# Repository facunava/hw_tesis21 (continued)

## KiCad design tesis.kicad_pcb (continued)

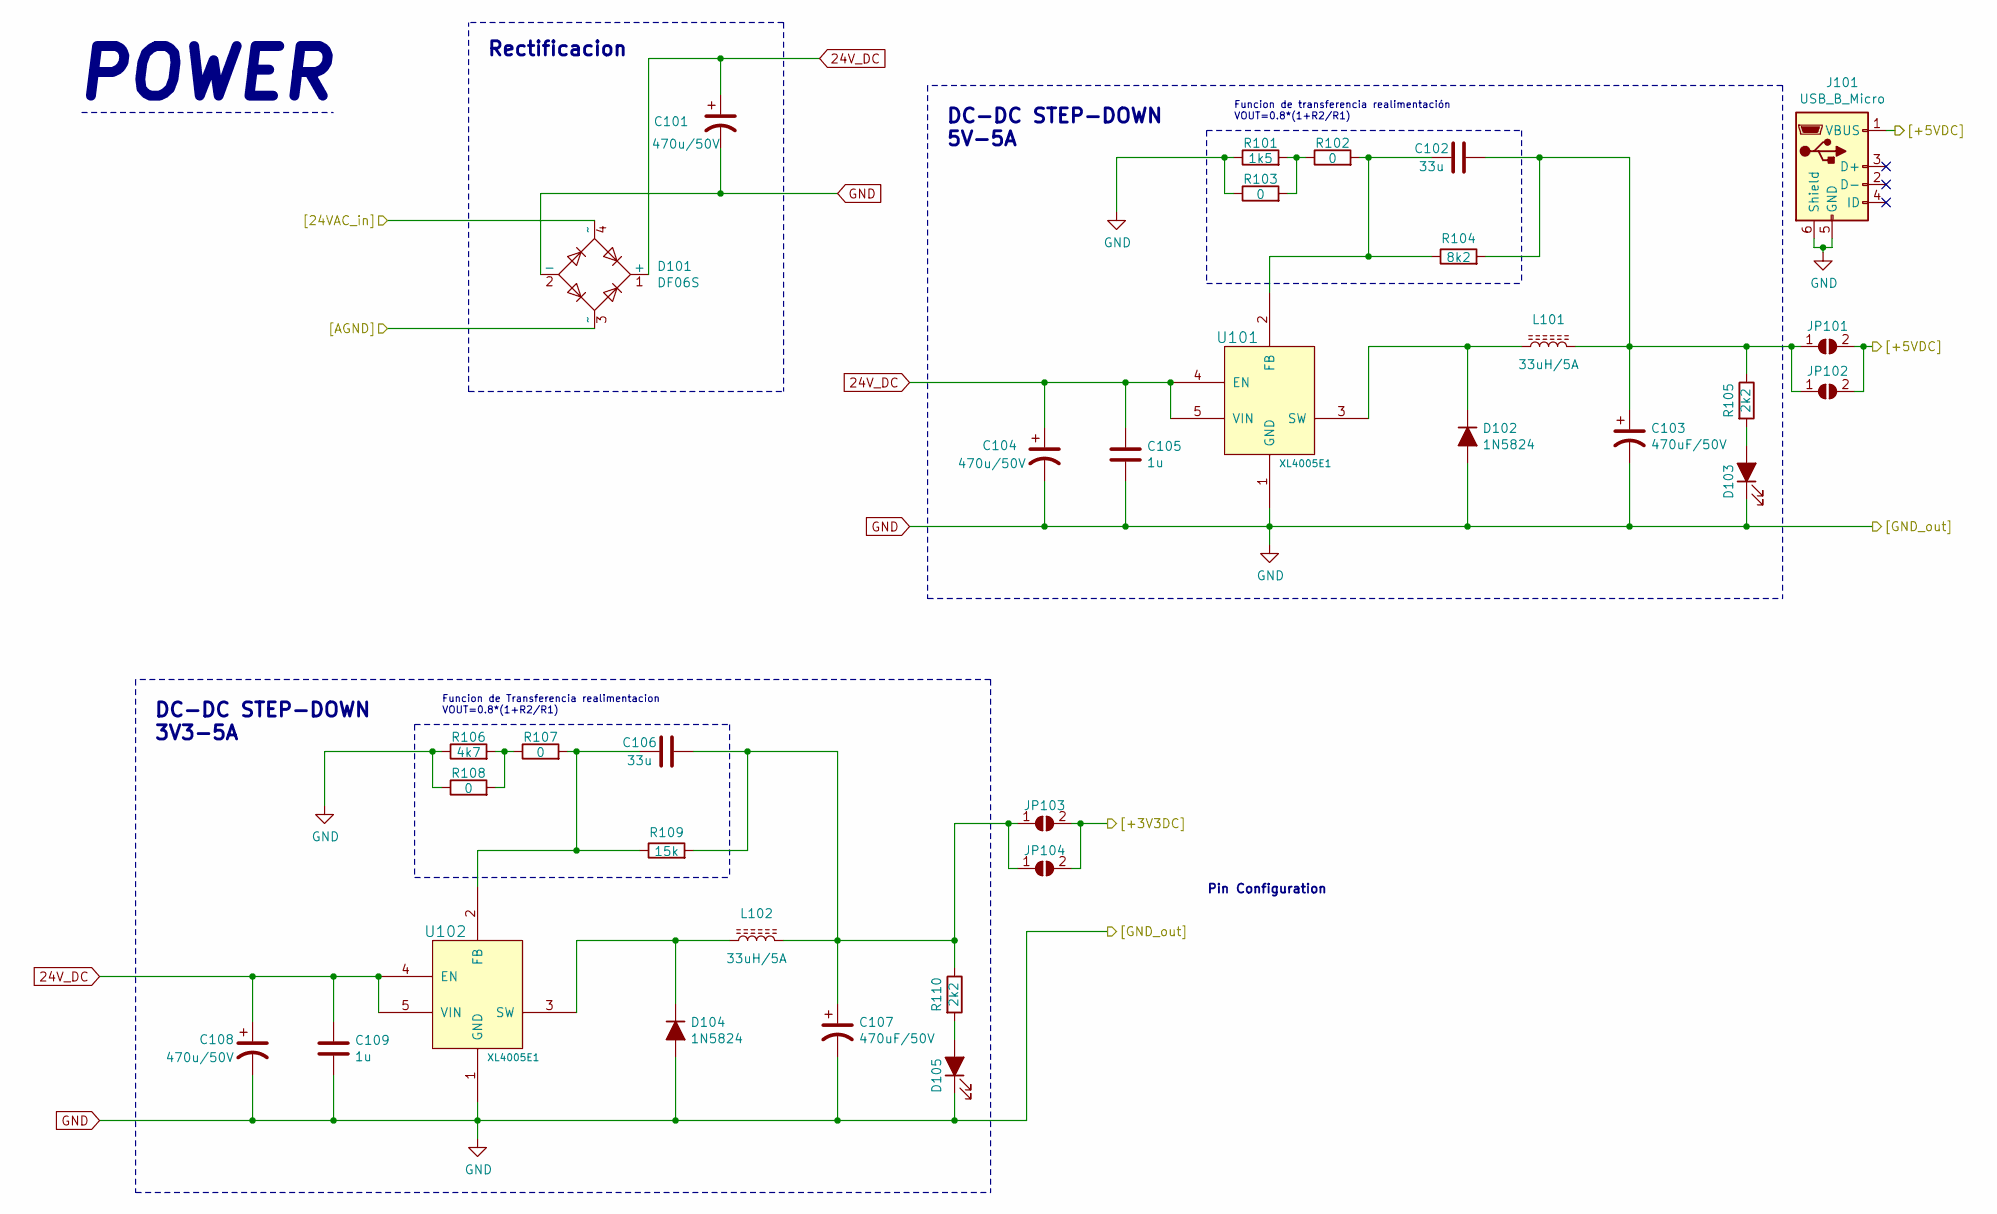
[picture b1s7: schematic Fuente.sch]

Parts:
C101: 470u/50V; CP_Elec_10x10
C102, C106: 33u; C_0805_2012Metric_Pad1.18x1.45mm_HandSolder
C103, C107: 470uF/50V; CP_Elec_8x10.5
C104, C108: 470u/50V; CP_Elec_8x10.5
C105, C109: 1u; C_0805_2012Metric_Pad1.18x1.45mm_HandSolder
D101: DF06S; Diode_Bridge_Vishay_DFSFlat
D102, D104: 1N5824; D_SMB_Handsoldering; PARTREV 2
D103, D105: green; LED_0805_2012Metric_Castellated
J101: USB_B_Micro; USB_Micro-B_Molex_47346-0001
JP101, JP102, JP103, JP104: jumper; SolderJumper-2_P1.3mm_Open_RoundedPad1.0x1.5mm
L101, L102: 33uH/5A; Coil_ferrite
R101: 1k5; R_0805_2012Metric_Pad1.20x1.40mm_HandSolder
R102, R103, R107, R108: 0; R_0805_2012Metric_Pad1.20x1.40mm_HandSolder
R104: 8k2; R_0805_2012Metric_Pad1.20x1.40mm_HandSolder
R105, R110: 2k2; R_0805_2012Metric_Pad1.20x1.40mm_HandSolder
R106: 4k7; R_0805_2012Metric_Pad1.20x1.40mm_HandSolder
R109: 15k; R_0805_2012Metric_Pad1.20x1.40mm_HandSolder
U101, U102: XL4005E1; TO-263-5_TabPin3

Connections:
24V_DC: C101.1, C104.1, C105.1, C108.1, C109.1, D101.1 (+), U101.4 (EN), U101.5 (VIN), U102.4 (EN), U102.5 (VIN)
+3V3: JP103.2 (B), JP104.2 (B); also elsewhere on the board
+5V: J101.1 (VBUS), JP101.2 (B), JP102.2 (B); also elsewhere on the board
/[24VAC_main]: D101.4 (~~); also elsewhere on the board
/[AGND_main]: D101.3 (~~); also elsewhere on the board
GND: C101.2, C103.2, C104.2, C105.2, C107.2, C108.2, C109.2, D101.2 (-), D102.2 (A), D103.1 (K), D104.2 (A), D105.1 (K), J101.5 (GND), J101.6 (Shield), R101.1, R103.1, R106.1, R108.1, U101.1 (GND), U102.1 (GND); also elsewhere on the board
unnamed: C102.1, C103.1, JP101.1 (A), JP102.1 (A), L101.2, R104.2, R105.1
unnamed: C102.2, R102.2, R104.1, U101.2 (FB)
unnamed: C106.1, C107.1, JP103.1 (A), JP104.1 (A), L102.2, R109.2, R110.1
unnamed: C106.2, R107.2, R109.1, U102.2 (FB)
unnamed: D102.1 (K), L101.1, U101.3 (SW)
unnamed: D103.2 (A), R105.2
unnamed: D104.1 (K), L102.1, U102.3 (SW)
unnamed: D105.2 (A), R110.2
unnamed: R101.2, R102.1, R103.2
unnamed: R106.2, R107.1, R108.2

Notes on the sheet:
POWER
DC-DC STEP-DOWN 3V3-5A
Funcion de Transferencia realimentacion VOUT=0.8*(1+R2/R1)
Rectificacion
Funcion de transferencia realimentación VOUT=0.8*(1+R2/R1)
DC-DC STEP-DOWN 5V-5A
Pin Configuration

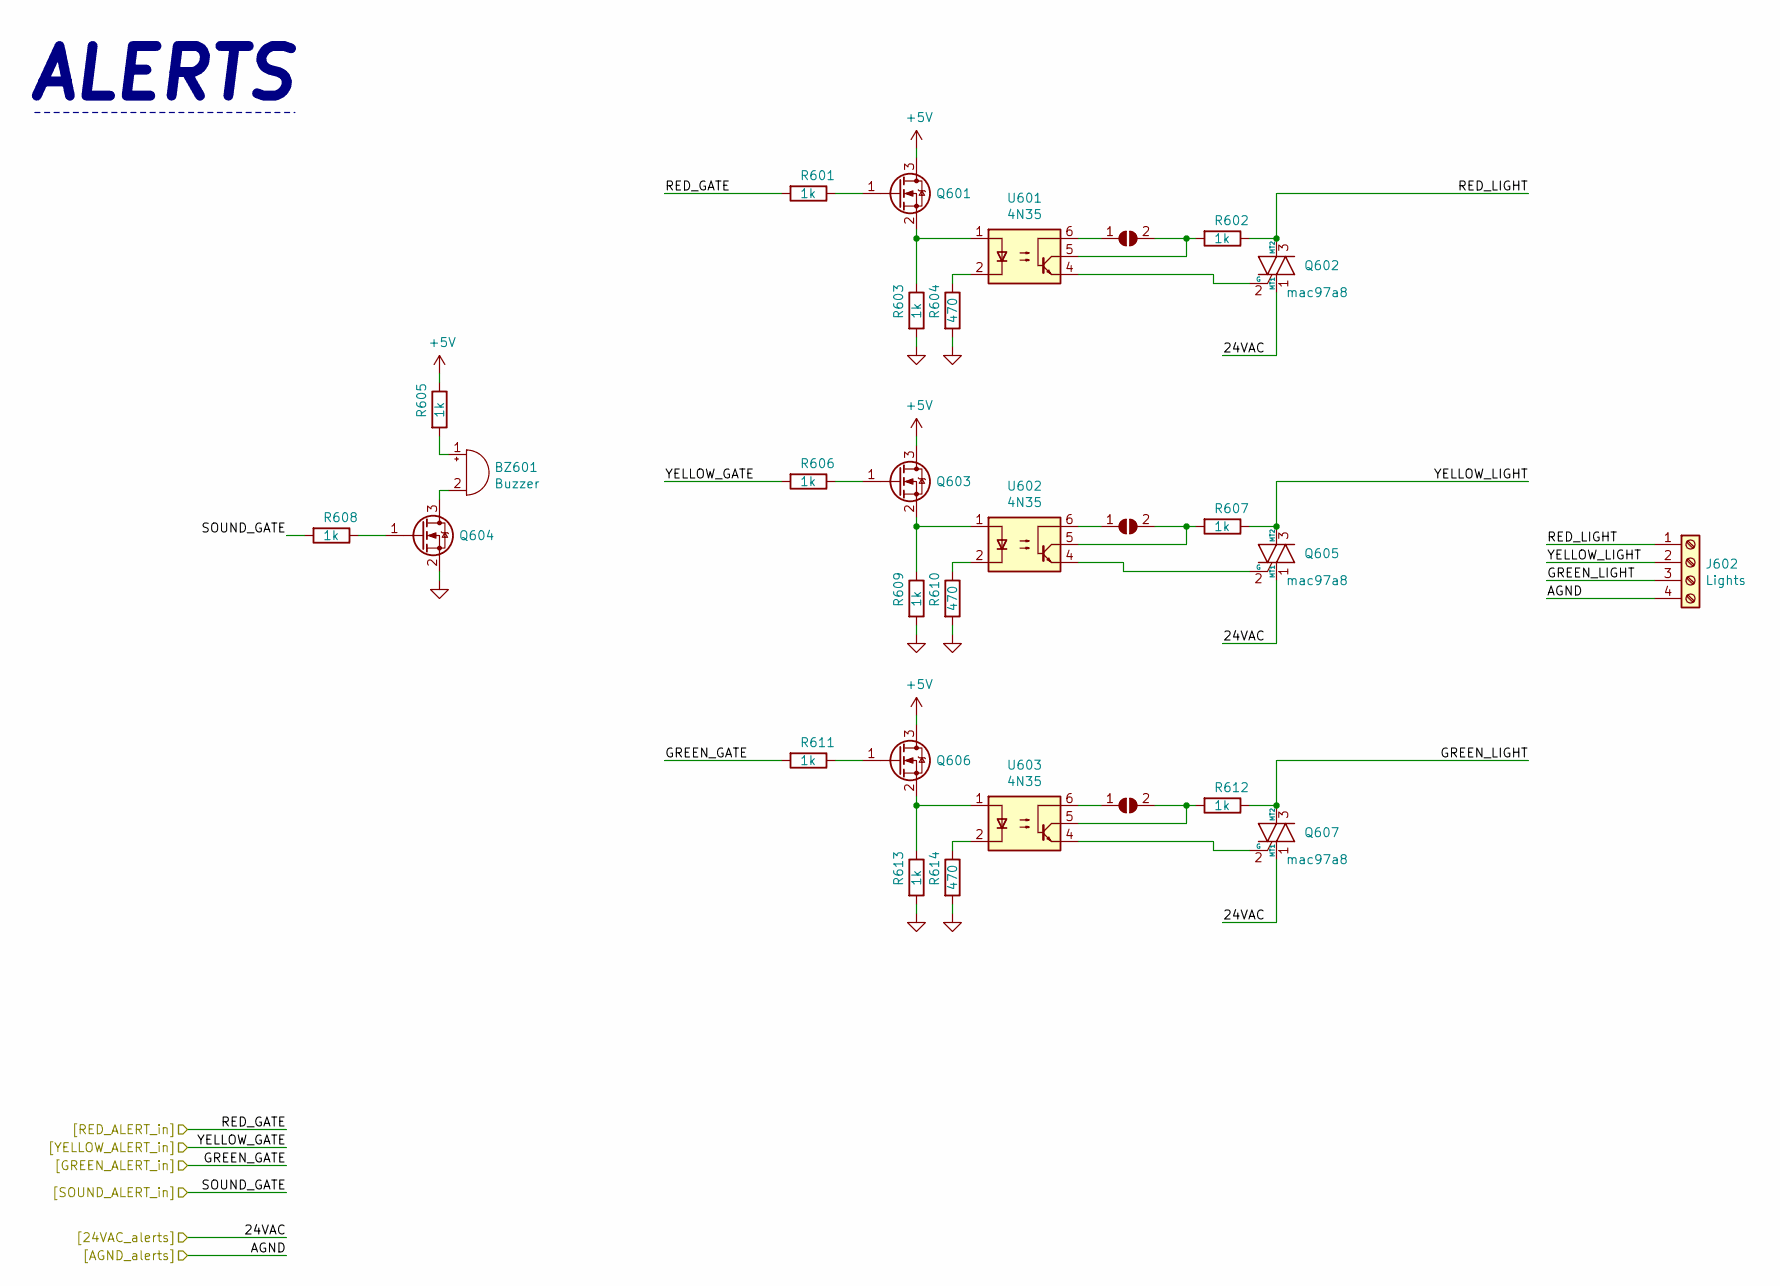
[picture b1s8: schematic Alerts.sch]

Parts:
BZ601: Buzzer; Buzzer_23x10
J602: Lights; TerminalBlock_Phoenix_MKDS-1,5-4-5.08_1x04_P5.08mm_Horizont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
JP601, JP602, JP603: jumper; SolderJumper-2_P1.3mm_Open_RoundedPad1.0x1.5mm
Q601, Q603, Q604, Q606: bss138; SOT-23
Q602, Q605, Q607: mac97a8; TO-92_Inline
R601, R602, R603, R605, R606, R607, R608, R609, R611, R612, R613: 1k; R_0805_2012Metric_Pad1.20x1.40mm_HandSolder
R604, R610, R614: 470; R_0805_2012Metric_Pad1.20x1.40mm_HandSolder
U601, U602, U603: 4N35; SMDIP-6_W7.62mm

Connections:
+5V: Q601.3 (D), Q603.3 (D), Q606.3 (D), R605.1; also elsewhere on the board
/Alerts/GREEN_LIGHT: J602.3, Q607.3 (MT2), R612.1
/Alerts/RED_LIGHT: J602.1, Q602.3 (MT2), R602.1
/Alerts/YELLOW_LIGHT: J602.2, Q605.3 (MT2), R607.1
/Alerts/[GREEN_ALERT_in]: R611.2; also elsewhere on the board
/Alerts/[RED_ALERT_in]: R601.2; also elsewhere on the board
/Alerts/[SOUND_ALERT_in]: R608.2; also elsewhere on the board
/Alerts/[YELLOW_ALERT_in]: R606.2; also elsewhere on the board
/[24VAC_main]: Q602.1 (MT1), Q605.1 (MT1), Q607.1 (MT1); also elsewhere on the board
/[AGND_main]: J602.4; also elsewhere on the board
GND: Q604.2 (S), R603.2, R604.2, R609.2, R610.2, R613.2, R614.2; also elsewhere on the board
unnamed: BZ601.1 (-), R605.2
unnamed: BZ601.2 (+), Q604.3 (D)
unnamed: JP601.1 (A), U601.6
unnamed: JP601.2 (B), R602.2, U601.5
unnamed: JP602.1 (A), U602.6
unnamed: JP602.2 (B), R607.2, U602.5
unnamed: JP603.1 (A), U603.6
unnamed: JP603.2 (B), R612.2, U603.5
unnamed: Q601.1 (G), R601.1
unnamed: Q601.2 (S), R603.1, U601.1
unnamed: Q602.2 (G), U601.4
unnamed: Q603.1 (G), R606.1
unnamed: Q603.2 (S), R609.1, U602.1
unnamed: Q604.1 (G), R608.1
unnamed: Q605.2 (G), U602.4
unnamed: Q606.1 (G), R611.1
unnamed: Q606.2 (S), R613.1, U603.1
unnamed: Q607.2 (G), U603.4
unnamed: R604.1, U601.2
unnamed: R610.1, U602.2
unnamed: R614.1, U603.2

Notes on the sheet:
ALERTS

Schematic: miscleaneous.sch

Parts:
G1: LOGO_SSaffron; smart_saffron
G2: LOGO_utn; logo_utn
G3: LOGO_azafran; azafran
G4: LOGO_arg; argentina
MH1, MH2, MH3, MH4: MountingHole; MountingHole_3.2mm_M3_Pad_Via
TP1: TestPoint; TestPoint_Plated_Hole_D2.0mm

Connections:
GND: TP1.1; also elsewhere on the board

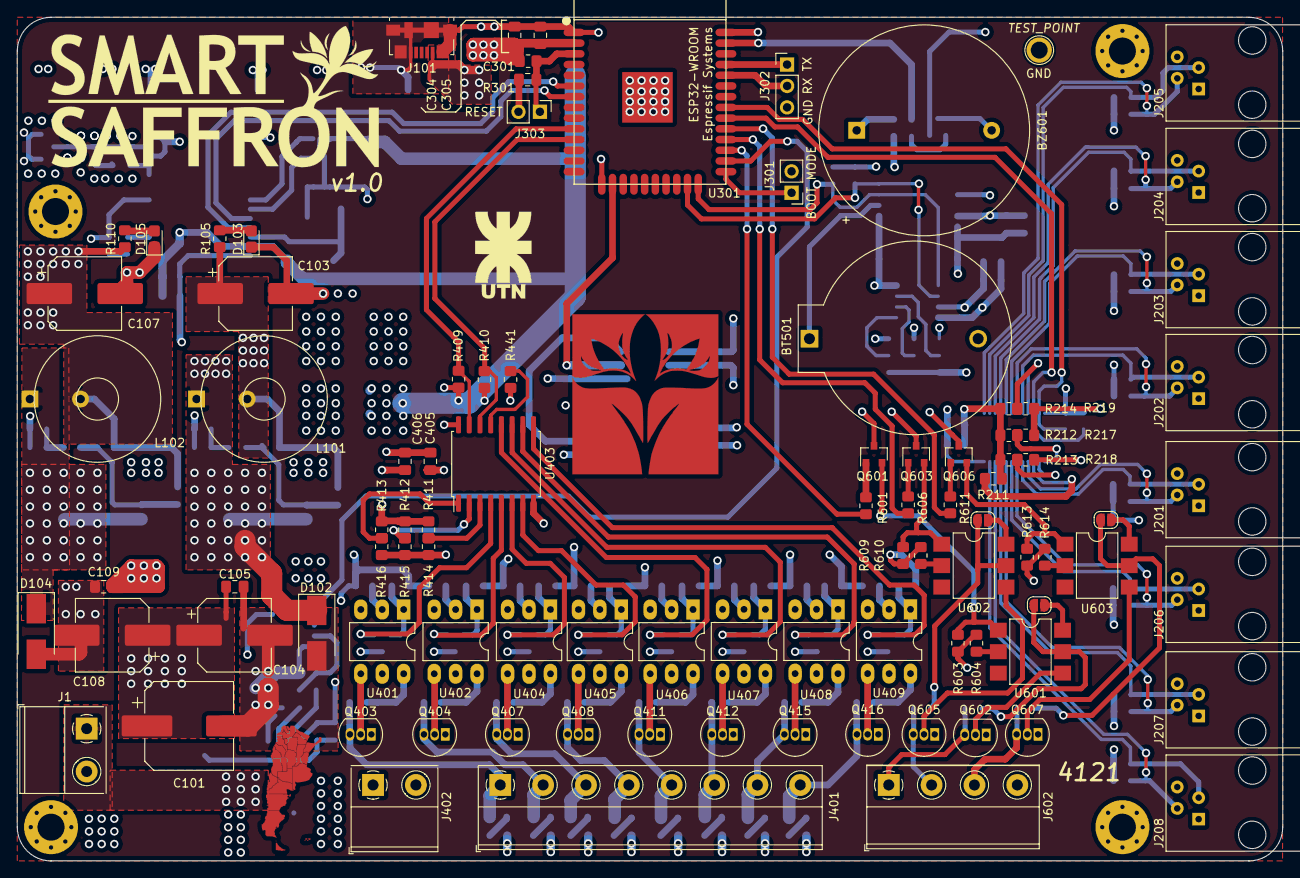
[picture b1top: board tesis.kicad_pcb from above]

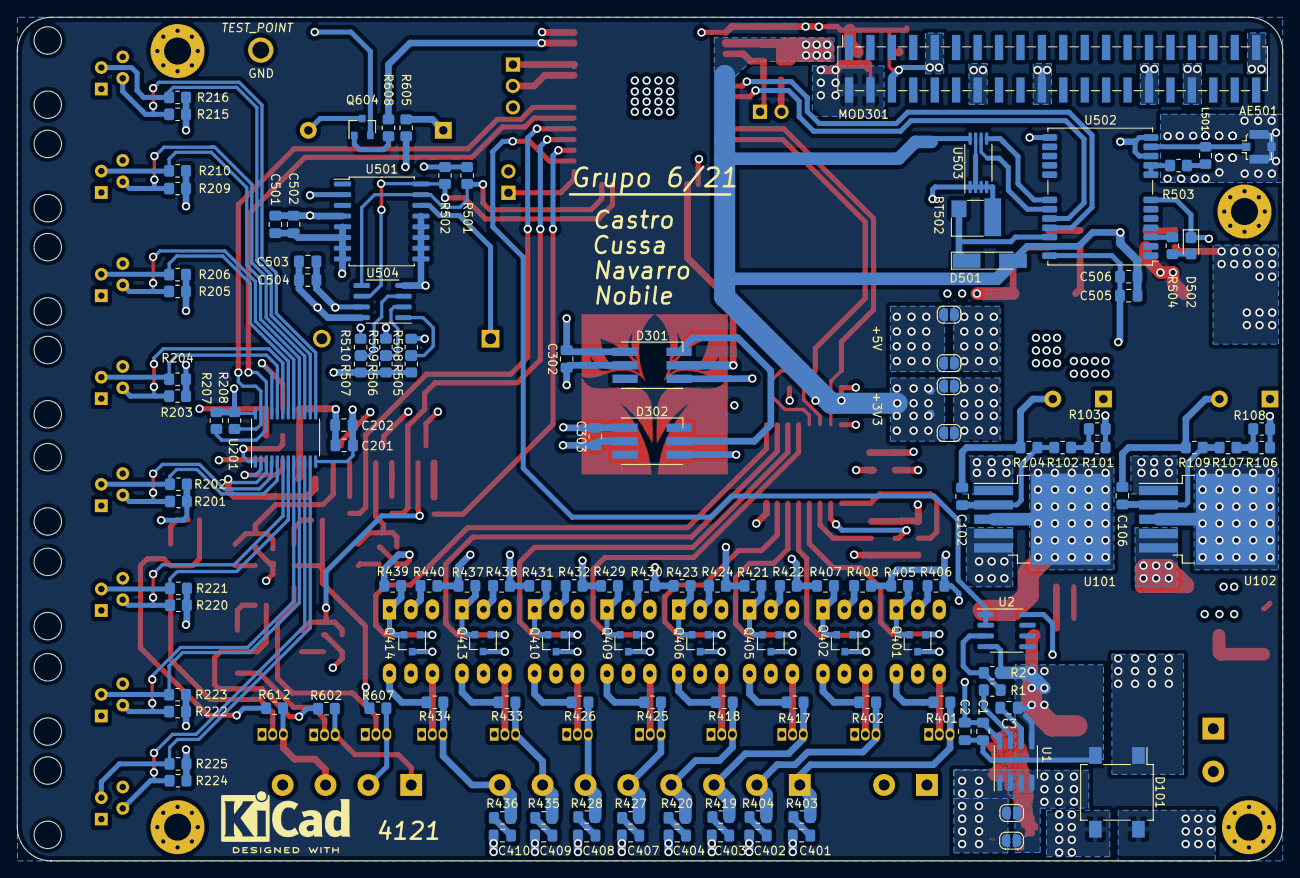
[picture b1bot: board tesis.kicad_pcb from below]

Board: 4 copper layers, 150.0 x 100.0 mm, 234 parts (131 on the bottom side), 155 nets.

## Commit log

2021-08-28 Backlink to CADLAB.io has been added.
2021-08-28 Primer commit, subo primeras carpetas.
2021-09-04 Create Power.sch
    Pagina de Fuente añadida
2021-09-08 del power
    borre Power porque no salia en KiCad
2021-09-08 create fuente
    Se creo el archivo fuente, se pusieron los componentes y se conectaron.
2021-09-10 Agrego proyectos de interes.
    Agrego proyecto RetroCIAA
    Agrego proyecto AXIOM
2021-09-11 Avance PCB [11/09/21]
    # Agrego avance inputs, outpus.
    # Se corrige referencia de esquematico Power.
2021-09-11 Se cargaron valores y fdt
2021-09-11 actualización
2021-09-12 Arreglos.
    * Arreglo referencias de address de salida(PCF8574)
2021-09-12 Probando-Desk
    sin cambios
2021-09-12 MOC3043 no MOC3041
    Cambiar componente
2021-09-14 Salidas está OK!
    Dejo nota en el kicad "Text"
2021-09-15 Agregado puente diodo
2021-09-18 Agregado fuente 3.3V
2021-09-18 Arreglo raiz de proyecto
2021-09-19 Fuente 3v3 agregada
2021-10-12 Agrego v1.0 de SmartSaffron
2021-10-13 Fixes PCB, reset esp32
2021-10-14 Revision
    * Acomodo los datos de F.Fab y B.Fab
    * Genero ibom
    * Exporto PDF e imagenes
2021-10-17 Fix por revision grupal
    *Fix de memoria de i2c, mal sda y scl
    *Fix inpunts sda y scl
2021-10-17 Version 1.0 compra en jlcpcb.
    *Se agregan gerbers e ibom de version de produccion.
2021-11-21 Agrego imagenes.
    * Se agregan las imagenes que utilizamos para la flor y el simbolo
    de argentina.
